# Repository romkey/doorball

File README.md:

# Doorball - Sensors for your door/mailbox/gate/trashbins...

Doorball is a [Furball](https://github.com/HomeBusProjects/furball)-variant which helps monitor motion and door or lid closure.

## Hardware

- TinyPico ESP32 board
- MPU9250 accelerometer
- contact sensor

## License

Doorball's software is licensed under the [MIT license](https://romkey.mit-license.org). Hardware is open source.

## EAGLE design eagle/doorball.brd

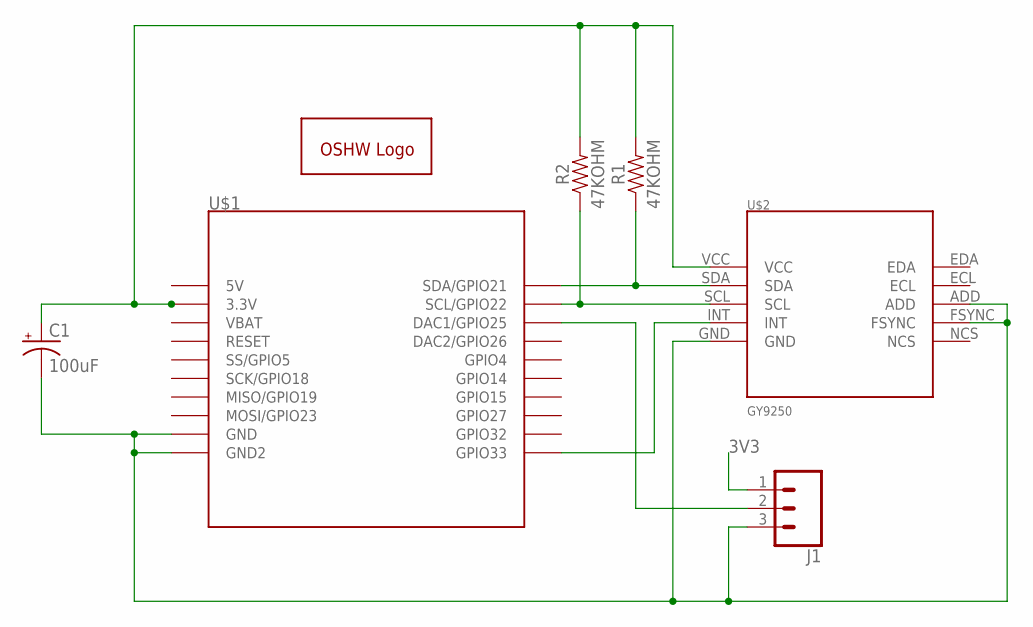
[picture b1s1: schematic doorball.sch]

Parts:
C1: 100uF; CPOL-RADIAL-2.5MM-6.5MM
GOLD_ORB_SM1: OSHWLOGOLOGO5MM; OSHW_5MM
J1: CONN_03; 1X03
R1, R2: 47KOHM; AXIAL-0.3-KIT
U$1: ESP23-TINY-PICO; ESP32-TINY-PICO
U$2: GY9250; GY9250BREAKOUT

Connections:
3V3: C1.1 (+), J1.1, R1.P$2 (2), R2.P$2 (2), U$1.3.3V, U$2.VCC
5V: U$1.5V
GND: C1.2 (-), J1.3, U$1.GND, U$1.GND@2 (GND2), U$2.ADD, U$2.FSYNC, U$2.GND
unnamed: R1.P$1 (1), U$1.SDA/GPIO21, U$2.SDA
unnamed: R2.P$1 (1), U$1.SCL/GPIO22, U$2.SCL
unnamed: J1.2, U$1.DAC1/GPIO25
unnamed: U$1.GPIO33, U$2.INT

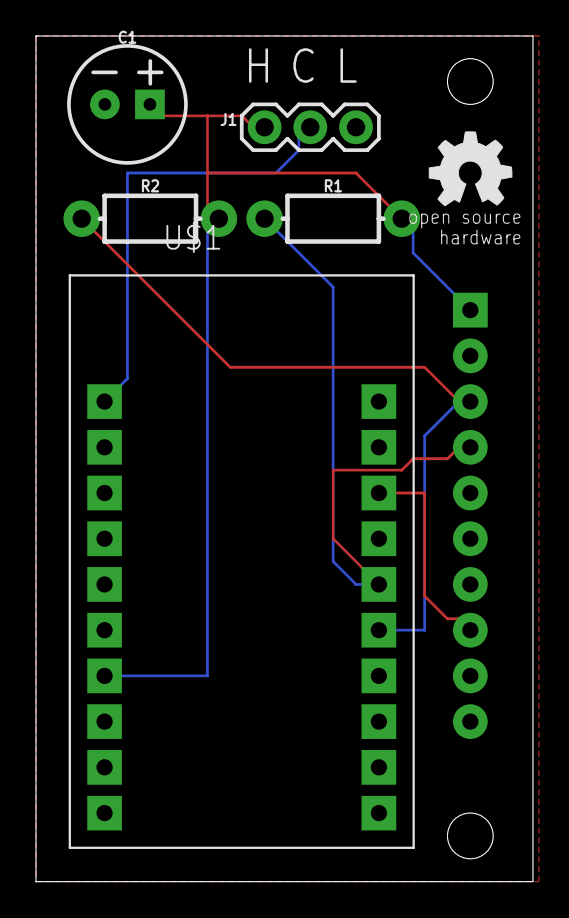
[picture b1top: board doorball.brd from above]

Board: 2 copper layers, 27.6 x 47.0 mm, 7 parts (1 on the bottom side), 6 nets.

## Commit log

2020-05-29 brief update to README

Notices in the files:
parts and their libraries:
SparkFun-Connectors: Licensing: Creative Commons ShareAlike 4.0 International - https://creativecommons.org/licenses/by-sa/4.0
